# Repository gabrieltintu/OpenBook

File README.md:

## © 2025 Gabriel-Claudiu TINTU

# OpenBook - E-Book Reader Project

## Table of Contents

1. [Block Diagram](#block-diagram)
2. [Bill of Materials (BOM)](#bill-of-materials-bom)
3. [Hardware Functionality and Components](#hardware-functionality-and-components)
   - [Main Controller](#main-controller)
   - [Display System](#display-system)
   - [Power Management](#power-management)
   - [Memory and Storage](#memory-and-storage)
   - [Sensors and Timing](#sensors-and-timing)
   - [Connectivity](#connectivity)
4. [ESP32-C6 Pin Usage](#esp32-c6-pin-usage)
5. [3D Representation](#3d-representation)

## Block Diagram

## Bill of Materials (BOM)
| Package                                      | Parts                                                                                             | Datasheet | Supplier  |
|----------------------------------------------|---------------------------------------------------------------------------------------------------|----------------|-----------------|
| ADAFRUIT_CHIP-LED0603                        | CHG_LED                                                                                           | [Link](https://eu.mouser.com/datasheet/2/216/AP1608SURCK-71562.pdf)      | [Link](https://eu.mouser.com/ProductDetail/Kingbright/AP1608SURCK?qs=VdjlWU%2FzoOEvYrd0H0exvQ%3D%3D)       |
| SJ                                           | SJ1                                                                                               | [Link](https://grabcad.com/library/solder-jumpers-1)      | [Link](https://grabcad.com/library/solder-jumpers-1)       |
| ESP32_WROVER_EAGLE-LTSPICE_R0402             | R1_PWRUSB, R1, R1_PINH1, R2-PINH, R2-PINH1, R5, R6, R7, R8, R9, R10, R_BOOT, R_CL1, R_RESET, R3, R1_PINH, R4, R_CHANGE, R_CAPACITOR, R2, R1_BAT, R2_BAT, R2_USB, R2_USB1                                                                                       | [Link](https://eu.mouser.com/datasheet/2/447/YAGEO_PYu_RC_Group_51_RoHS_L_12-3313492.pdf)      | [Link](https://eu.mouser.com/ProductDetail/YAGEO/RC0402FR-07100KL?qs=mnq%2FyloZIXzTlUn7JAHSWg%3D%3D)       |
| ESP32_WROVER_EAGLE-LTSPICE_C0402             | C1, C2, C4_USB, C6, C8, C9, C10, C_DELAY, EPD_C5, EPD_C1, EPD_C2, EPD_C6, EPD_C7, EPD_C8, EPD_C9, EPD_C10, EPD_C11, EPD_C12, C7, C5, C4, C1_BAT, C1_BAT1, C1_BAT2, C2_BAT, C5_USB                                                           | [Link](https://eu.mouser.com/datasheet/2/447/upy_gphc_x5r_4v_to_50v-3461255.pdf)      | [Link](https://eu.mouser.com/ProductDetail/YAGEO/CC0402MRX5R5BB106?qs=zEY9bCHj09eCmUJdZuS5Lg%3D%3D)       |
| RCL_CT3528                                   | C3                                                                                                 | [Link](https://eu.mouser.com/datasheet/2/40/TAJ-3165264.pdf)      | [Link](https://eu.mouser.com/ProductDetail/KYOCERA-AVX/TAJB475K025RNJ?qs=mgX5NEyWO4Sl7CIvkz4Jiw%3D%3D)       |
| 112ATAARR03ATTEND                            | J4                                                                                                 | [Link](https://store.comet.bg/download-file.php?id=27596)      | [Link](https://store.comet.srl.ro/Catalogue/Product/43497/)       |
| ESP32_WROVER_SPARKFUN-DISCRETESEMI_SOT23-3    | Q1, Q2                                                                                             | [Link](https://www.diodes.com/assets/Datasheets/DMG2305UX.pdf)      | [Link](https://eu.mouser.com/ProductDetail/Diodes-Incorporated/DMG2305UX-7?qs=L1DZKBg7t5F%2FNBHrjfxC%252Bg%3D%3D)       |
| IND_4828-WE-TPC_WRE                         | L1                                                                                                 | [Link](https://www.we-online.com/components/products/datasheet/744043680.pdf)      | [Link](https://eu.mouser.com/ProductDetail/Wurth-Elektronik/744043680?qs=PGXP4M47uW6VkZq%252BkzjrHA%3D%3D)       |
| SOT95P280X125-5N                             | IC1                                                                                                | [Link](https://fscdn.rohm.com/en/products/databook/datasheet/ic/power/voltage_detector/bd52xxg-e.pdf)      | [Link](https://eu.mouser.com/ProductDetail/ROHM-Semiconductor/BD5229G-TR?qs=4kLU8WoGk0vvnhrrYwdszw%3D%3D)       |
| MYBUTTON                                     | BOOT_BUTTON, CHANGE_BUTTON, RESET_BUTTON                                                         | [Link](https://www3.panasonic.biz/ac/e_download/control/switch/light-touch/catalog/sw_lt_eng_3529s_side.pdf?f_cd=402906)      | [Link](https://eu.mouser.com/ProductDetail/Panasonic/EVQ-P7L01P?qs=rJ%252BziJWpyszWhhNszc02jQ%3D%3D)       |
| CAPCP3225X100N                               | C10_SUPERCAP                                                                                        | [Link](https://eu.mouser.com/datasheet/2/360/Seiko_Instruments_MicroBattery_E_20230330_2024Jan_-3561061.pdf)      | [Link](https://eu.mouser.com/ProductDetail/Seiko-Semiconductors/CPH3225A?qs=3etwrb1wR%252BhUOph6lAO7eg%3D%3D)       |
| SOIC127P1032X265-16N                         | U3                                                                                                 | [Link](https://eu.mouser.com/datasheet/2/609/DS3231-3421123.pdf)      | [Link](https://eu.mouser.com/ProductDetail/Analog-Devices-Maxim-Integrated/DS3231SN?qs=1eQvB6Dk1vhUlr8%2FOrV0Fw%3D%3D)       |
| XCVR_ESP32-C6-WROOM-1-N8                    | U2                                                                                                 | [Link](https://eu.mouser.com/datasheet/2/891/Espressif_ESP32_C6_WROOM_1__Datasheet_V0_1_PRELIMI-3239987.pdf)      | [Link](https://eu.mouser.com/ProductDetail/Espressif-Systems/ESP32-C6-WROOM-1-N8?qs=8Wlm6%252BaMh8ST02Gmwp74cw%3D%3D)       |
| ESP32C6_VARISTOR_CT/CN1812                  | PFMF.050.1                                                                                        | [Link](https://eu.mouser.com/datasheet/2/358/typ_PFMF-1275918.pdf)      | [Link](https://eu.mouser.com/ProductDetail/Schurter/PFMF.050.2?qs=1auRipcfynCums5v1iucSA%3D%3D)       |
| ESP32_WROVER_AVX---SD0805S020S1R0_AVX_SD0805S020S1R0_0 | D2, D7                                                                                             | [Link](https://eu.mouser.com/datasheet/2/40/schottky-3165252.pdf)      | [Link](https://eu.mouser.com/ProductDetail/KYOCERA-AVX/SD0805S020S1R0?qs=jCA%252BPfw4LHbpkAoSnwrdjw%3D%3D)       |
| ESP32_WROVER_BME680_PSON80P300X300X100-8N    | SENSOR2                                                                                           | [Link](https://www.bosch-sensortec.com/media/boschsensortec/downloads/datasheets/bst-bme680-ds001.pdf)      | [Link](https://store.comet.srl.ro/Catalogue/Product/50164/)       |
| ESP32_WROVER_SPARKFUN-IC-POWER_SOT23-5       | U0                                                                                                 | [Link](https://eu.mouser.com/datasheet/2/268/MCP73831_Family_Data_Sheet_DS20001984H-3441711.pdf)      | [Link](https://eu.mouser.com/ProductDetail/Microchip-Technology/MCP73831T-4ADI-OT?qs=hH%252BOa0VZEiBTiqxSV9eepQ%3D%3D)       |
| FH34SRJ24S05SH99                             | J1                                                                                                 | [Link](https://eu.mouser.com/datasheet/2/760/xc6220-3371556.pdf)      | [Link](https://eu.mouser.com/ProductDetail/Torex-Semiconductor/XC6220A331MR-G?qs=AsjdqWjXhJ8ZSWznL1J0gg%3D%3D)       |
| SON50P200X200X80-9N                          | U4                                                                                                 | [Link](https://eu.mouser.com/datasheet/2/609/MAX17048_MAX17049-3469099.pdf)      | [Link](https://eu.mouser.com/ProductDetail/Analog-Devices-Maxim-Integrated/MAX17048G%2bT10?qs=D7PJwyCwLAoGnnn8jEPRBQ%3D%3D)       |
| SOD3716X135N                                 | D3, D4, D5                                                                                         | [Link](https://eu.mouser.com/datasheet/2/40/schottky-3165252.pdf)      | [Link](https://eu.mouser.com/ProductDetail/KYOCERA-AVX/SD0805S020S1R0?qs=jCA%252BPfw4LHbpkAoSnwrdjw%3D%3D)       |
| DIOC1608X36N                                 | D6, D8, D9, D10, D11, D12                                                                           | [Link](https://www.littelfuse.com/assetdocs/pulseguard-esd-suppressors-pgb1-datasheet?assetguid=8a337998-d54d-466b-be4e-dc5bcd1f9321)      | [Link](https://eu.mouser.com/ProductDetail/Littelfuse/PGB1010603MR?qs=gu7KAQ731URLg4GSnNNN7Q%3D%3D)       |
| JST04_1MM_RA                                 | J3                                                                                                 | [Link](https://eu.mouser.com/datasheet/2/813/Qwiic_Connector_Datasheet-1223982.pdf)      | [Link](https://eu.mouser.com/ProductDetail/SparkFun/PRT-14417?qs=wd5RIQLrsJhgdz%2FpmZ%2F3GQ%3D%3D)       |
| SAMACSYS_PARTS_USB4110GFA                    | J2                                                                                                 | [Link](https://eu.mouser.com/datasheet/2/837/GCT_USB4110_Product_Drawing___20k_cycles-3455479.pdf)      | [Link](https://eu.mouser.com/ProductDetail/GCT/USB4110-GF-A?qs=KUoIvG%2F9IlYiZvIXQjyJeA%3D%3D)       |
| SOT65P210X110-3N                             | Q3                                                                                                 | [Link](https://www.vishay.com/doc?63399)      | [Link](https://eu.mouser.com/ProductDetail/Vishay-Semiconductors/SI1308EDL-T1-GE3?qs=bX1%252BNvsK%2FBramh9tgpOaEw%3D%3D)       |
| SOT95P280X145-6N                             | D1                                                                                                 | [Link](https://eu.mouser.com/datasheet/2/389/usblc6_2sc6y-1852505.pdf)      | [Link](https://eu.mouser.com/ProductDetail/STMicroelectronics/USBLC6-2SC6Y?qs=gNDSiZmRJS%2FOgDexvXkdow%3D%3D)       |
| SON127P600X800X80-9N                         | U1                                                                                                 | [Link](https://eu.mouser.com/datasheet/2/949/Winbond_W25Q512JV_Datasheet-3240039.pdf)      | [Link](https://eu.mouser.com/ProductDetail/Winbond/W25Q512JVEIQ?qs=l7cgNqFNU1jw6svr3at6tA%3D%3D)       |
| SOT95P280X120-5N                             | IC4                                                                                                | [Link](https://eu.mouser.com/datasheet/2/760/xc6220-3371556.pdf)      | [Link](https://eu.mouser.com/ProductDetail/Torex-Semiconductor/XC6220A331MR-G?qs=AsjdqWjXhJ8ZSWznL1J0gg%3D%3D)       |

## Hardware Functionality and Components

### Main Controller

* ESP32-C6-WROOM-1-N8: The core microcontroller module that manages all device functions

### Display System

* E-Paper Display: Connected via a 24-pin FH34SRJ-24S-0.5SH connector (J1)
* E-Paper Drive Circuit: Custom circuitry for driving the e-paper display
* Display Type Selector: Allows for configuration of different e-paper display types

### Power Management

* LDO Voltage Regulator (XC6220A331MR-G): Provides regulated 3.3V power supply for the system
* Battery Charge Controller (MCP73831): Manages charging of the Li-Po battery
* Battery Charge Level Monitor (MAX17048G+T10): Monitors battery charge level and status
* USB C Connector: For power input and data communication
* ESD Protection (USBLC6-2SC6Y): Protects USB data lines from electrostatic discharge

### Memory and Storage

* External NOR Flash (W25Q512JVEIQ): 64MB flash memory for data storage
* SD Card Slot: For expandable storage

### Sensors and Timing

* Environmental Sensor (BME688): Measures temperature, humidity, pressure, and gas resistance
* RTC Module (DS3231SN): Real-time clock for accurate timekeeping

### Connectivity

* Qwiic/Stemma QT Connector: For I2C-based expansion modules
* USB-C: For data communication and power

## ESP32-C6 Pin Usage

| **Pin** | **Function** | **Component** | **Purpose** |
|-----|----------|-----------|---------|
| EN  | RESET | Reset button | System reset input |
| IO0 | INT_RTC | RTC | RTC interrupt for timing events |
| IO1 | 32KHZ | RTC | 32kHz clock signal from RTC |
| IO2 | MISO | SPI Bus | Data input from SPI peripherals |
| IO3 | EPD_BUSY | E-Paper Display | Monitor display ready status |
| IO4 | SS_SD | SD Card | SD card chip select |
| IO5 | EPD_DC | E-Paper Display | Display data/command selection |
| IO6 | SCK | SPI Bus | SPI clock signal |
| IO7 | MOSI | SPI Bus | Data output to SPI peripherals |
| IO8 | GPIO8 | General Purpose | Auxiliary functions |
| IO9 | IO/BOOT | Boot button | Boot mode selection |
| IO10 | EPD_CS | E-Paper Display | Display chip select |
| IO11 | FLASH_CS | External NOR Flash | Flash memory chip select |
| IO12 | USB_D- | USB Interface | USB data negative line |
| IO13 | USB_D+ | USB Interface | USB data positive line |
| IO15 | IO/CHANGE | Change button | Status change detection |
| IO16/TXD0 | TX | Serial Debug | UART transmit |
| IO17/RXD0 | RX | Serial Debug | UART receive |
| IO18 | RTC_RST | RTC | RTC reset control |
| IO19 | I2C_PW | I2C Bus | I2C devices power control |
| IO20 | EPD_3V3_C | E-Paper Display | Display power control |
| IO21 | SDA | I2C Bus | I2C data line |
| IO22 | SCL | I2C Bus | I2C clock line |
| IO23 | EPD_RST | E-Paper Display | Display reset control |

## 3D Representation

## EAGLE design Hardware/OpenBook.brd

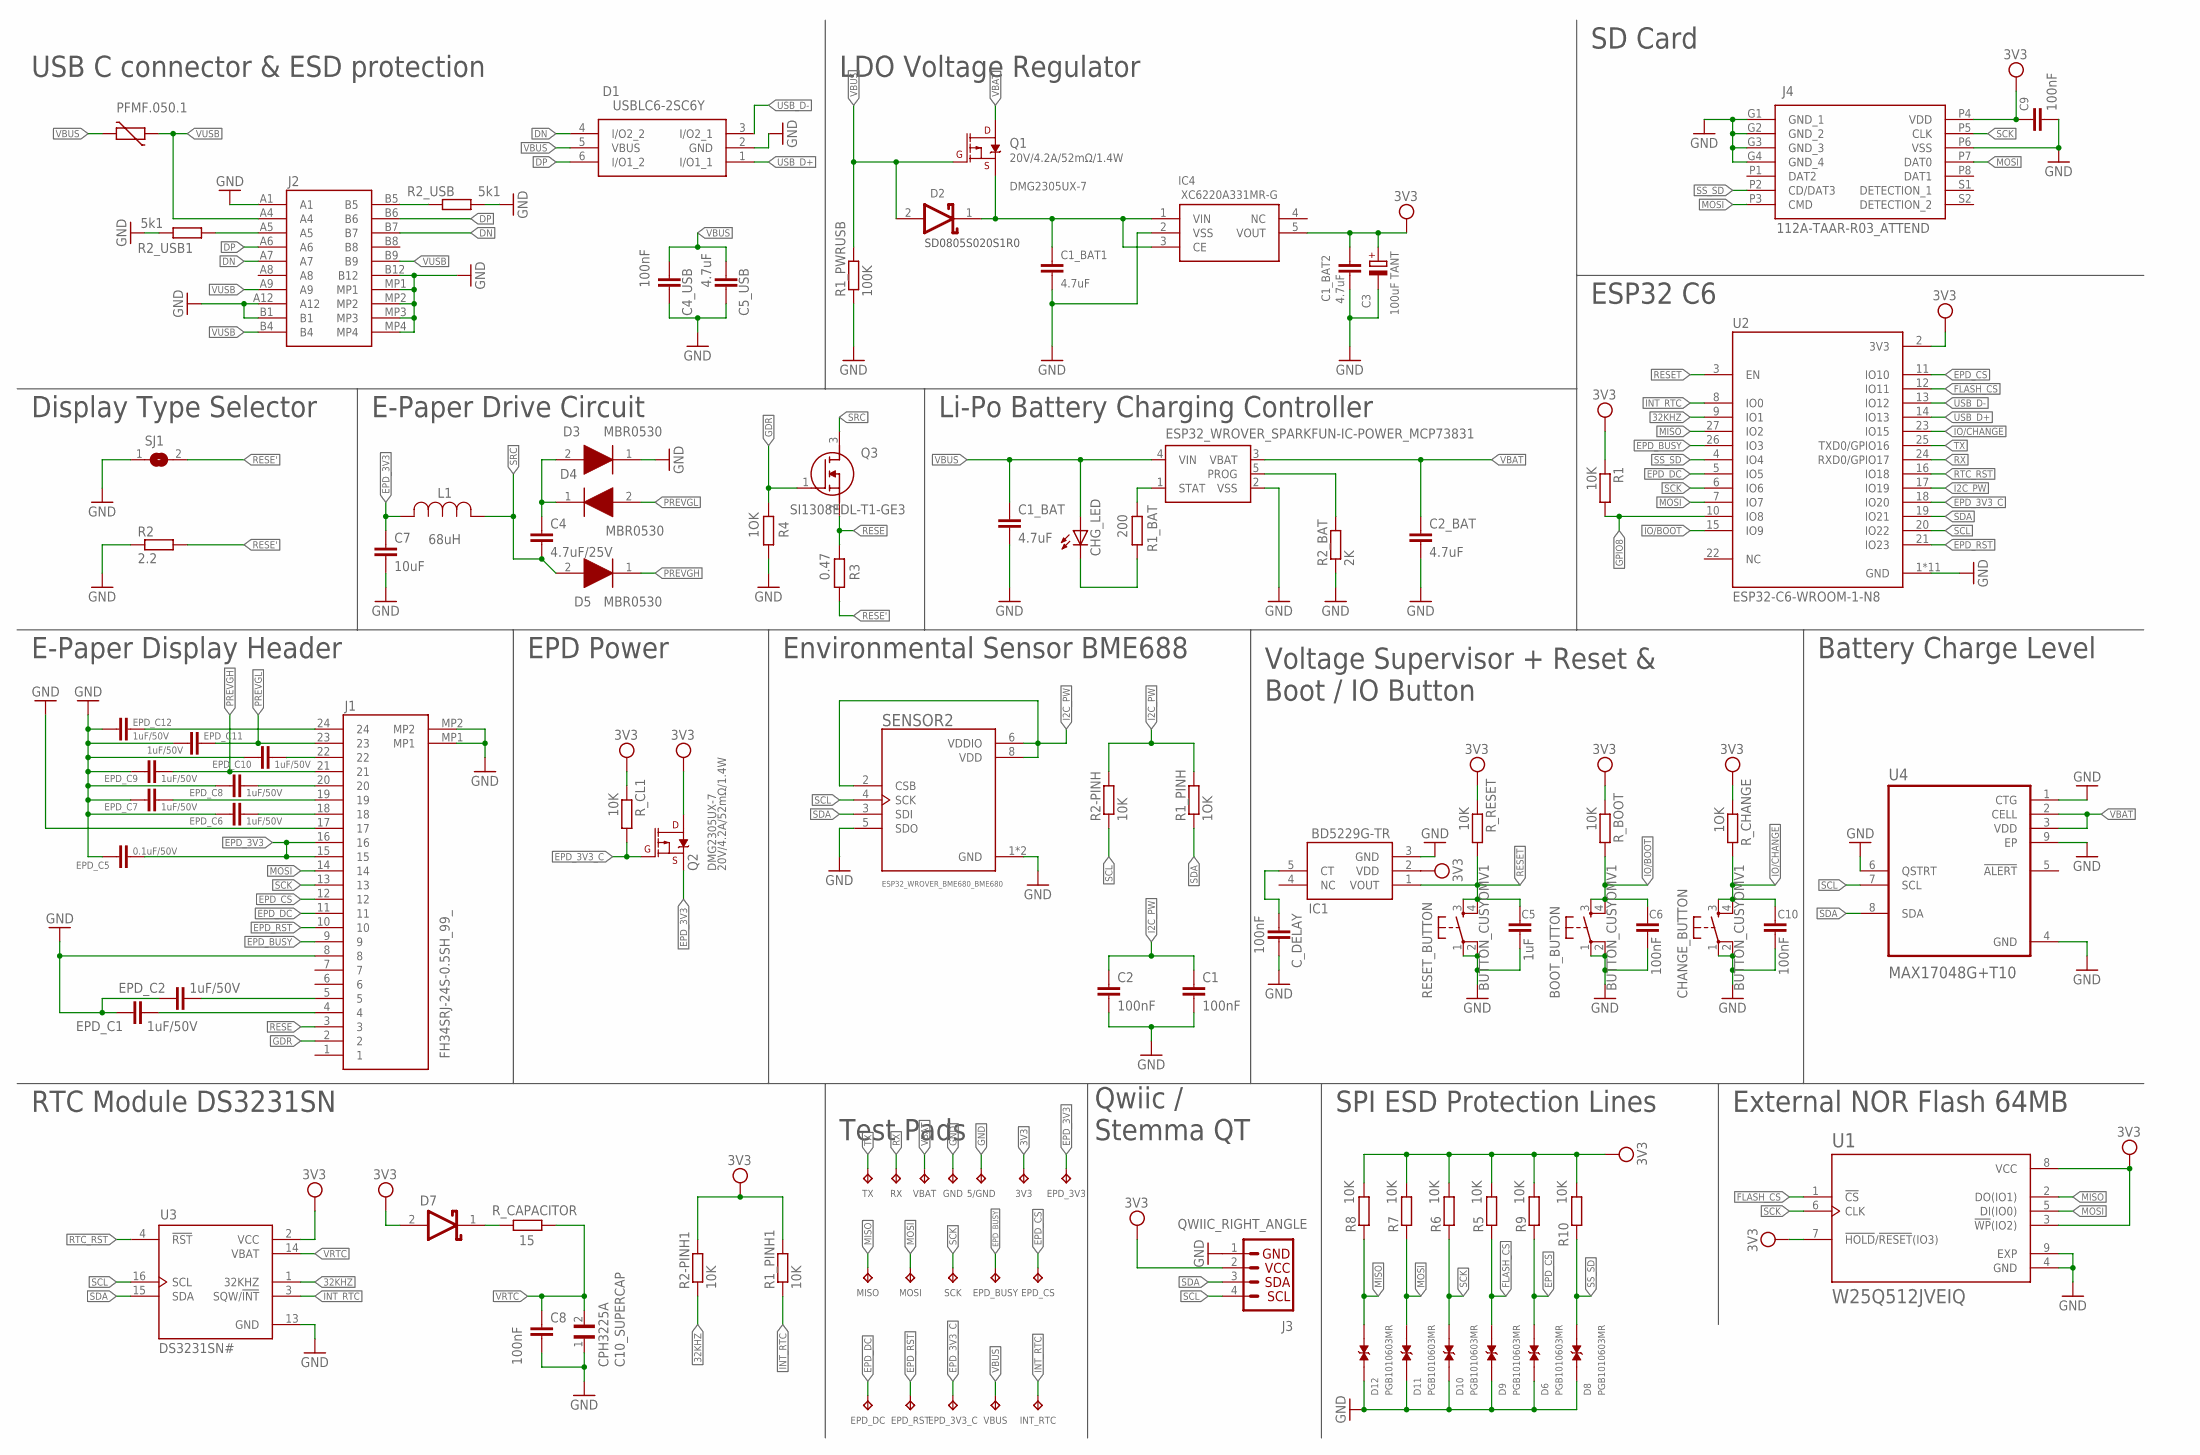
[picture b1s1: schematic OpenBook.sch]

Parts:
3V3, 5/GND: TPTP20R; TP20R
BOOT_BUTTON: BUTTON_CUSYOMV1; MYBUTTON
C1, C2, C4_USB, C6, C8, C9, C10: 100nF; ESP32_WROVER_EAGLE-LTSPICE_C0402
C1_BAT, C1_BAT1, C1_BAT2, C2_BAT, C5_USB: 4.7uF; ESP32_WROVER_EAGLE-LTSPICE_C0402
C3: 100uF TANT; RCL_CT3528
C4: 4.7uF/25V; ESP32_WROVER_EAGLE-LTSPICE_C0402
C5: 1uF; ESP32_WROVER_EAGLE-LTSPICE_C0402
C7: 10uF; ESP32_WROVER_EAGLE-LTSPICE_C0402
C10_SUPERCAP: CPH3225A; CAPCP3225X100N
CHANGE_BUTTON: BUTTON_CUSYOMV1; MYBUTTON
CHG_LED: ADAFRUIT_LEDCHIP-LED0603; ADAFRUIT_CHIP-LED0603
C_DELAY: 100nF; ESP32_WROVER_EAGLE-LTSPICE_C0402
D1: USBLC6-2SC6Y; SOT95P280X145-6N
D2, D7: ESP32_WROVER_AVX---SD0805S020S1R0_AVX_SD0805S020S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; ESP32_WROVER_AVX---SD0805S020S1R0_AVX_SD0805S020S1R0_0
D3, D4, D5: MBR0530; SOD3716X135N
D6, D8, D9, D10, D11, D12: PGB1010603MR; DIOC1608X36N
EPD_3V3, EPD_3V3_C: TPTP20R; TP20R
EPD_BUSY: TPTP20R; TP20R
EPD_C1, EPD_C2, EPD_C6, EPD_C7, EPD_C8, EPD_C9, EPD_C10, EPD_C11, EPD_C12: 1uF/50V; ESP32_WROVER_EAGLE-LTSPICE_C0402
EPD_C5: 0.1uF/50V; ESP32_WROVER_EAGLE-LTSPICE_C0402
EPD_CS: TPTP20R; TP20R
EPD_DC: TPTP20R; TP20R
EPD_RST: TPTP20R; TP20R
GND: TPTP20R; TP20R
IC1: BD5229G-TR; SOT95P280X125-5N
IC4: XC6220A331MR-G; SOT95P280X120-5N
INT_RTC: TPTP20R; TP20R
J1: FH34SRJ-24S-0.5SH_99_; FH34SRJ24S05SH99
J2: SAMACSYS_PARTS_USB4110-GF-A; SAMACSYS_PARTS_USB4110GFA
J3: QWIIC_RIGHT_ANGLE; JST04_1MM_RA
J4: 112A-TAAR-R03_ATTEND; 112ATAARR03ATTEND
L1: 744043680IND_4828-WE-TPC_WRE; IND_4828-WE-TPC_WRE
MISO: TPTP20R; TP20R
MOSI: TPTP20R; TP20R
PFMF.050.1: ESP32C6_VARISTORCN1812; ESP32C6_VARISTOR_CT/CN1812
Q1, Q2: 20V/4.2A/52mΩ/1.4W; ESP32_WROVER_SPARKFUN-DISCRETESEMI_SOT23-3
Q3: SI1308EDL-T1-GE3; SOT65P210X110-3N
R1, R1_PINH1, R2-PINH, R2-PINH1, R5, R6, R7, R8, R9, R10: 10K; ESP32_WROVER_EAGLE-LTSPICE_R0402
R1_BAT: 200; ESP32_WROVER_EAGLE-LTSPICE_R0402
R1_PINH, R4: 1OK; ESP32_WROVER_EAGLE-LTSPICE_R0402
R1_PWRUSB: 100K; ESP32_WROVER_EAGLE-LTSPICE_R0402
R2: 2.2; ESP32_WROVER_EAGLE-LTSPICE_R0402
R2_BAT: 2K; ESP32_WROVER_EAGLE-LTSPICE_R0402
R2_USB, R2_USB1: 5k1; ESP32_WROVER_EAGLE-LTSPICE_R0402
R3: 0.47; ESP32_WROVER_EAGLE-LTSPICE_R0402
RESET_BUTTON: BUTTON_CUSYOMV1; MYBUTTON
RX: TPTP20R; TP20R
R_BOOT: 10K; ESP32_WROVER_EAGLE-LTSPICE_R0402
R_CAPACITOR: 15; ESP32_WROVER_EAGLE-LTSPICE_R0402
R_CHANGE: 1OK; ESP32_WROVER_EAGLE-LTSPICE_R0402
R_CL1: 10K; ESP32_WROVER_EAGLE-LTSPICE_R0402
R_RESET: 10K; ESP32_WROVER_EAGLE-LTSPICE_R0402
SCK: TPTP20R; TP20R
SENSOR2: ESP32_WROVER_BME680_BME680; ESP32_WROVER_BME680_PSON80P300X300X100-8N
SJ1: SJ
TX: TPTP20R; TP20R
U0: ESP32_WROVER_SPARKFUN-IC-POWER_MCP73831; ESP32_WROVER_SPARKFUN-IC-POWER_SOT23-5
U1: W25Q512JVEIQ; SON127P600X800X80-9N
U2: ESP32-C6-WROOM-1-N8; XCVR_ESP32-C6-WROOM-1-N8
U3: DS3231SN#; SOIC127P1032X265-16N
U4: MAX17048G+T10; SON50P200X200X80-9N
VBAT: TPTP20R; TP20R
VBUS: TPTP20R; TP20R

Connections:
3V3: 3V3.TP, C1_BAT2.1, C3.+, C9.1, D7.2 (ANODE), IC1.2 (VDD), IC4.5 (VOUT), J3.2, J4.P4 (VDD), Q2.3 (D), R1.1, R1_PINH1.2, R2-PINH1.2, R5.2, R6.2, R7.2, R8.2, R9.2, R10.2, R_BOOT.1, R_CHANGE.1, R_CL1.1, R_RESET.1, U1.3 (!WP!(IO2)), U1.7 (!HOLD!/!RESET!(IO3)), U1.8 (VCC), U2.2 (3V3), U3.2 (VCC)
32KHZ: R2-PINH1.1, U2.9 (IO1), U3.1 (32KHZ)
DN: D1.4 (I/O2_2), J2.A7, J2.B7
DP: D1.6 (I/O1_2), J2.A6, J2.B6
EPD_3V3: C7.1, EPD_3V3.TP, EPD_C5.1, J1.15, J1.16, L1.2, Q2.2 (S)
EPD_3V3_C: EPD_3V3_C.TP, Q2.1 (G), R_CL1.2, U2.18 (IO20)
EPD_BUSY: EPD_BUSY.TP, J1.9, U2.26 (IO3)
EPD_CS: D6.2, EPD_CS.TP, J1.12, R9.1, U2.11 (IO10)
EPD_DC: EPD_DC.TP, J1.11, U2.5 (IO5)
EPD_RST: EPD_RST.TP, J1.10, U2.21 (IO23)
FLASH_CS: D9.2, R5.1, U1.1 (!CS), U2.12 (IO11)
GDR: J1.2, Q3.1 (G), R4.2
GND: 5/GND.TP, BOOT_BUTTON.1, BOOT_BUTTON.2, C1.2, C1_BAT.2, C1_BAT1.2, C1_BAT2.2, C2.2, C2_BAT.2, C3.-, C4_USB.2, C5.2, C5_USB.2, C6.2, C7.2, C8.2, C9.2, C10.2, C10_SUPERCAP.1, CHANGE_BUTTON.1, CHANGE_BUTTON.2, C_DELAY.2, D1.2 (GND), D4.1 (K), D6.1, D8.1, D9.1, D10.1, D11.1, D12.1, EPD_C1.2, EPD_C2.2, EPD_C5.2, EPD_C6.2, EPD_C7.2, EPD_C8.2, EPD_C9.2, EPD_C10.2, EPD_C11.2, EPD_C12.2, GND.TP, IC1.3 (GND), IC4.2 (VSS), J1.8, J1.17, J1.MP1, J1.MP2, J2.A1, J2.A12, J2.B1, J2.B12, J2.MP1, J2.MP2, J2.MP3, J2.MP4, J3.1, J4.G1 (GND_1), J4.G2 (GND_2), J4.G3 (GND_3), J4.G4 (GND_4), J4.P6 (VSS), R1_PWRUSB.1, R2.1, R2_BAT.1, R2_USB.2, R2_USB1.1, R4.1, RESET_BUTTON.1, RESET_BUTTON.2, SENSOR2.1 (GND), SENSOR2.5 (SDO), SENSOR2.7 (GND), SJ1.1, U0.2 (VSS), U1.4 (GND), U1.9 (EXP), U2.1 (GND), U2.28 (GND), U2.29_1 (GND), U2.29_2 (GND), U2.29_3 (GND), U2.29_4 (GND), U2.29_5 (GND), U2.29_6 (GND), U2.29_7 (GND), U2.29_8 (GND), U2.29_9 (GND), U3.13 (GND), U4.1 (CTG), U4.4 (GND), U4.6 (QSTRT), U4.9 (EP)
GPIO8: R1.2, U2.10 (IO8)
I2C_PW: C1.1, C2.1, R1_PINH.2, R2-PINH.2, SENSOR2.2 (CSB), SENSOR2.6 (VDDIO), SENSOR2.8 (VDD), U2.17 (IO19)
INT_RTC: INT_RTC.TP, R1_PINH1.1, U2.8 (IO0), U3.3 (SQW/!INT)
IO/BOOT: BOOT_BUTTON.3, BOOT_BUTTON.4, C6.1, R_BOOT.2, U2.15 (IO9)
IO/CHANGE: C10.1, CHANGE_BUTTON.3, CHANGE_BUTTON.4, R_CHANGE.2, U2.23 (IO15)
MISO: D12.2, MISO.TP, R8.1, U1.2 (DO(IO1)), U2.27 (IO2)
MOSI: D11.2, J1.14, J4.P3 (CMD), J4.P7 (DAT0), MOSI.TP, R7.1, U1.5 (DI(IO0)), U2.7 (IO7)
unnamed: J2.A5, R2_USB1.2
unnamed: J2.B5, R2_USB.1
unnamed: C1_BAT1.1, D2.1 (CATHODE), IC4.1 (VIN), IC4.3 (CE), Q1.2 (S)
unnamed: R1_BAT.2, U0.1 (STAT)
unnamed: C4.1, D3.1 (K), D4.2 (A)
unnamed: CHG_LED.C, R1_BAT.1
unnamed: D7.1 (CATHODE), R_CAPACITOR.2
unnamed: R2_BAT.2, U0.5 (PROG)
unnamed: EPD_C12.1, J1.24
unnamed: C_DELAY.1, IC1.5 (CT)
unnamed: EPD_C10.1, J1.22
unnamed: EPD_C7.1, J1.19
unnamed: EPD_C8.1, J1.20
unnamed: EPD_C6.1, J1.18
unnamed: EPD_C1.1, J1.4
unnamed: EPD_C2.1, J1.5
PREVGH: D5.1 (K), EPD_C9.1, J1.21
PREVGL: D3.2 (A), EPD_C11.1, J1.23
RESE: J1.3, Q3.2 (S), R3.2
RESE': R2.2, R3.1, SJ1.2
RESET: C5.1, IC1.1 (VOUT), RESET_BUTTON.3, RESET_BUTTON.4, R_RESET.2, U2.3 (EN)
RTC_RST: U2.16 (IO18), U3.4 (!RST)
RX: RX.TP, U2.24 (RXD0/GPIO17)
SCK: D10.2, J1.13, J4.P5 (CLK), R6.1, SCK.TP, U1.6 (CLK), U2.6 (IO6)
SCL: J3.4, R2-PINH.1, SENSOR2.4 (SCK), U2.20 (IO22), U3.16 (SCL), U4.7 (SCL)
SDA: J3.3, R1_PINH.1, SENSOR2.3 (SDI), U2.19 (IO21), U3.15 (SDA), U4.8 (SDA)
SRC: C4.2, D5.2 (A), L1.1, Q3.3 (D)
SS_SD: D8.2, J4.P2 (CD/DAT3), R10.1, U2.4 (IO4)
TX: TX.TP, U2.25 (TXD0/GPIO16)
USB_D+: D1.1 (I/O1_1), U2.14 (IO13)
USB_D-: D1.3 (I/O2_1), U2.13 (IO12)
VBAT: C2_BAT.1, Q1.3 (D), U0.3 (VBAT), U4.2 (CELL), U4.3 (VDD), VBAT.TP
VBUS: C1_BAT.1, C4_USB.1, C5_USB.1, CHG_LED.A, D1.5 (VBUS), D2.2 (ANODE), PFMF.050.1.2, Q1.1 (G), R1_PWRUSB.2, U0.4 (VIN), VBUS.TP
VRTC: C8.1, C10_SUPERCAP.2, R_CAPACITOR.1, U3.14 (VBAT)
VUSB: J2.A4, J2.A9, J2.B4, J2.B9, PFMF.050.1.1

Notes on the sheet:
USB C connector & ESD protection
LDO Voltage Regulator
SD Card
ESP32 C6
Battery Charge Level
External NOR Flash 64MB
SPI ESD Protection Lines
Qwiic / Stemma QT
Test Pads
RTC Module DS3231SN
E-Paper Display Header
Display Type Selector
E-Paper Drive Circuit
Li-Po Battery Charging Controller
Environmental Sensor BME688
EPD Power
Voltage Supervisor + Reset & Boot / IO Button
DMG2305UX-7
SD0805S020S1R0
68uH

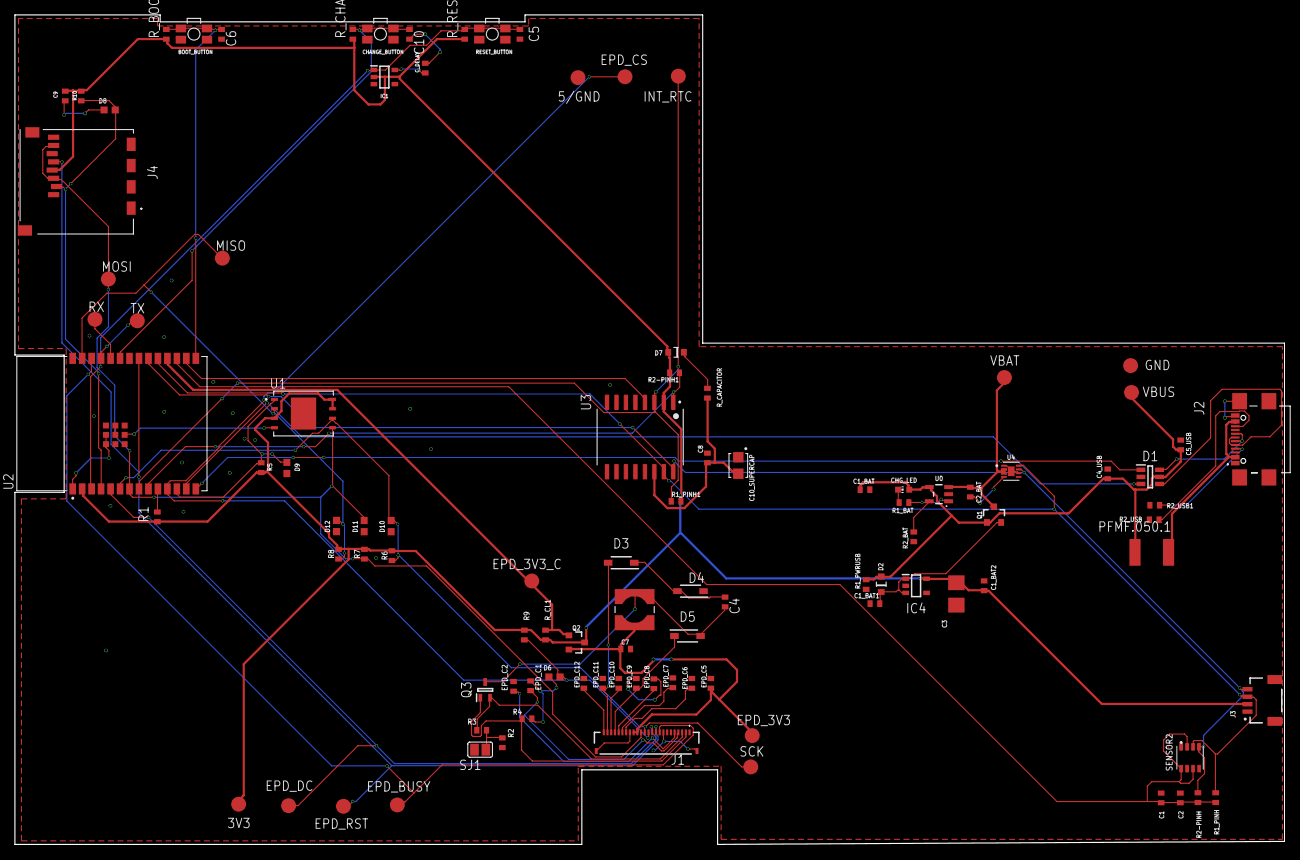
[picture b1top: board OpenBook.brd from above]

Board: 2 copper layers, 170.2 x 111.2 mm, 103 parts (0 on the bottom side), 55 nets.

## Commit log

2025-04-05 init
2025-04-06 add README
2025-04-06 create LICENSE
2025-04-14 fixed pcb thickness and unfilled areas in GND plane

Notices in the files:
parts and their libraries:
COPYRIGHT: Copyright (C) 2024 Ultra Librarian. All rights reserved.
